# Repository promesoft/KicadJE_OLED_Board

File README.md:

# KicadJE_OLED_Board
uP Boards that uses I2C SSD1306 for OLED Display faceplate

# Purpose
uProcessor board in eurorack units with an SSD1306 OLED display, two rotary dials/pots, two audio inputs, two cv inputs and two outputs. Must match the Faceplate - KicadJE_OLED_Face.
## Board 1 - ATMega32A
Adjustment:  
2 x Encoder  

CV Input:  
2 x ADC AC/DC couple with optional level adj to match 0-5V ADC

Gate or Input Audio:  
2 x ADC AC/DC couple with optional level adj to match 0-5V ADC

Output CV:  
2 x PWM output through 3 pole active LP  
+-10v

Programming Interface:  
ISP  
Serial  

# Status - Initiated
## Initial 
| Stage  | Detail | Status |
| ------------- | ------------- | ------------- |
| create material  | sch | OK
| | pcb | OK
| | gerber | OK
| production |  |  OK
|  | produced  | OK
|  | delivered | OK
## Preliminary validation
| Test  | Detail | Status |
| ------------- | ------------- | ------------- |
| Initial Inspection | | ok |
| Mechanical Inspection | needs longer pins to OLED | ok |
| Initial Technical Test | Board 1 |  |
| Initial Product Test | Board1 |  |

## Secondary validation
| Test  | Detail | Status |
| ------------- | ------------- |------------- |
| Product Test | 1 | |
| Quality | 1 | |
| Long Term Product Test |  |  |
| Power Draw |  | 

## Errata
### Errata - 

## Issues and Notes
### 

# Pictures

# Schematic
## Sch 1

#Software

# Analysis
## Diag 1

## Prototype

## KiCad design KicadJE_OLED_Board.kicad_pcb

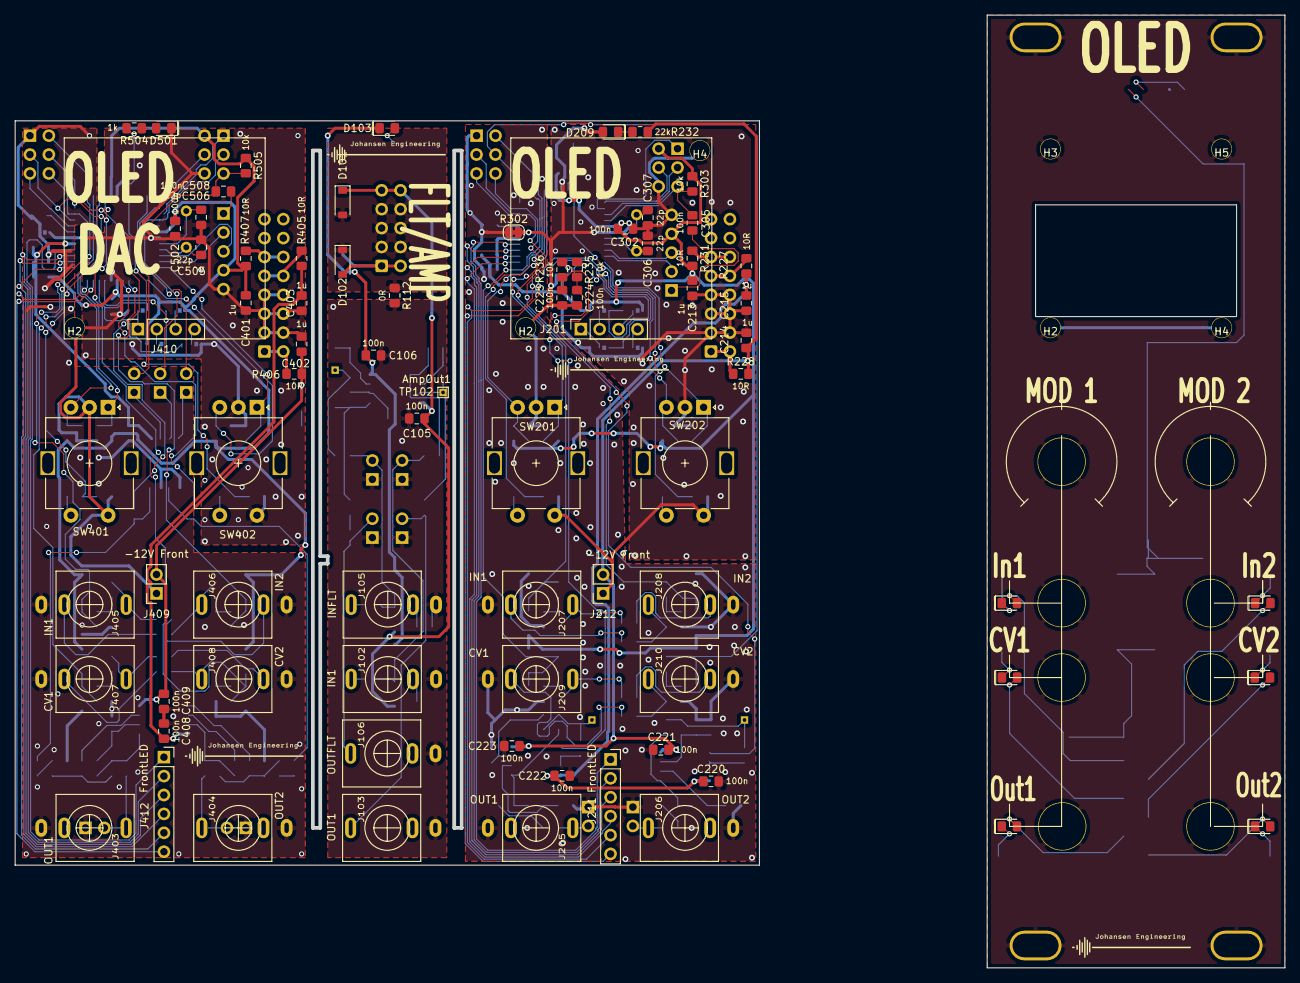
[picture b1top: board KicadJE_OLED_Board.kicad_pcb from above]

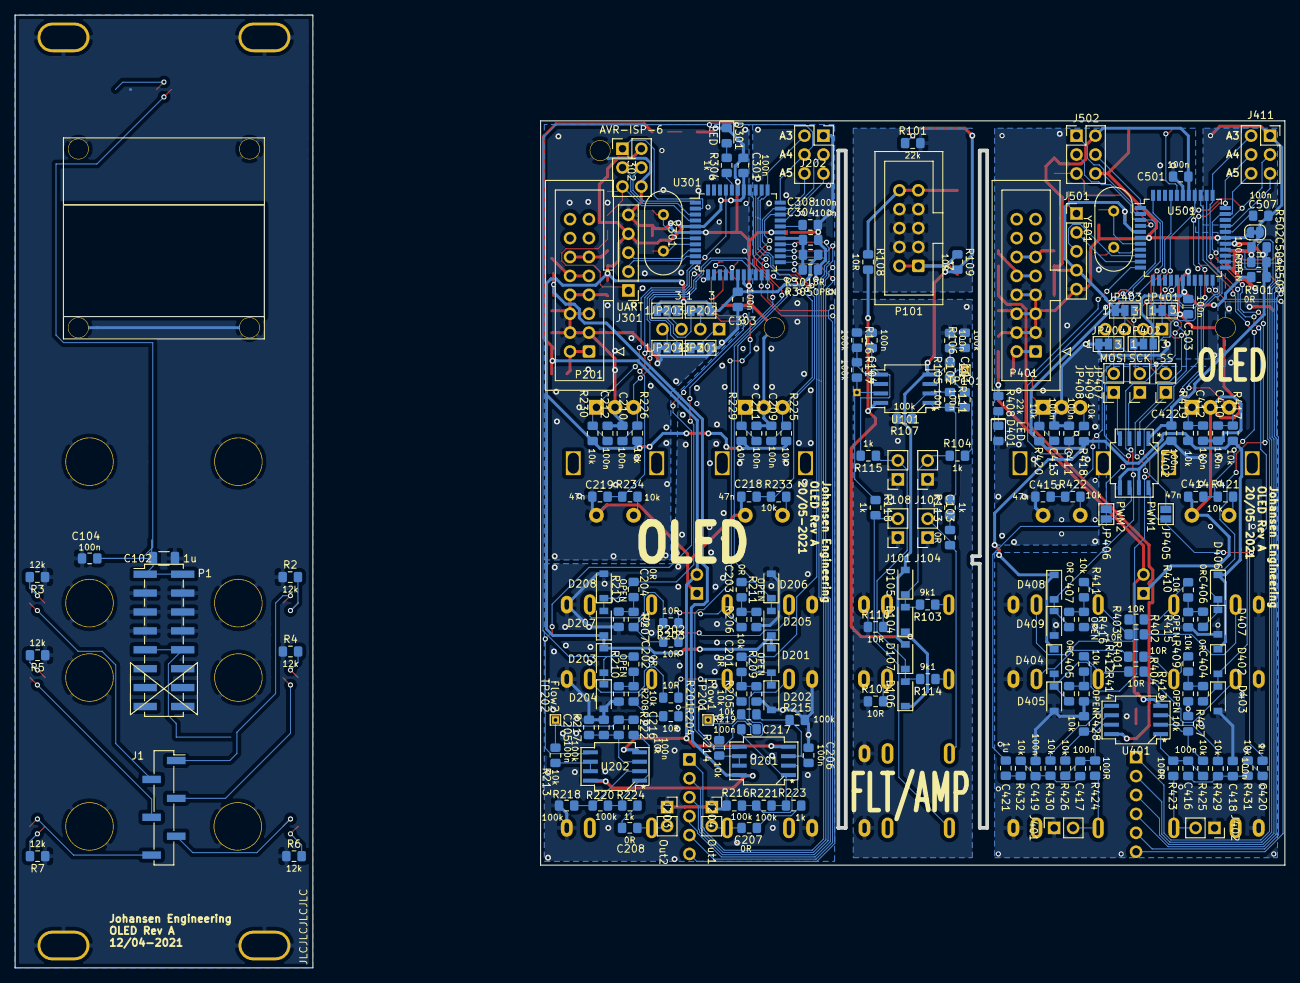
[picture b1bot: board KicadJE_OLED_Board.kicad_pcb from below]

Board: 2 copper layers, 100.0 x 100.0 mm, 296 parts (203 on the bottom side), 184 nets.

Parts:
C101, C102#2, C104, C104#2, C105, C106, C205, C206, C209, C210, C211, C212, C216, C217, C220, C221, C222, C223, C224, C225, C301, C302, C303, C304, C305, C308, C408, C409, C410, C411, C412, C413, C416, C417, C418, C419, C422, C501, C502, C503, C504, C507, C508: 100n; C_0805_AJ
C102: 1u; C_1206_3216Metric
C103, C201, C202, C203, C204, C207, C208, C404, C405, C406, C407: 0R; C_0805_AJ
C213, C214, C215, C401, C402, C403, C420, C421: 1u; C_0805_AJ
C218, C219, C414, C415: 47n; C_0805_AJ
C306, C307, C505, C506: 22p; C_0805_AJ
D4, D5, D6, D7, D8, D9, D103, D209, D301, D401, D501: LED; D_0805_AJ
D101, D102, D104, D105, D106, D107, D201, D202, D203, D204, D205, D206, D207, D208, D402, D403, D404, D405, D406, D407, D408, D409: 1N1007; D_SOD-123
H2, H2#2, H2#3, H3, H4, H4#2, H5: OLED; M2.7_Plated
H102, H103, H104, H105: MountingHole_Pad; MountingHole_Eurorack3
J1: LED 1-6; PinHeader_1x06_P2.54mm_Vertical_SMD_Pin1Right
J101, J204, J402: Out1; PinSocket_1x02_P2.54mm_Vertical
J102, J207, J405: IN1; PJ301SM
J103, J205, J403: OUT1; PJ301SM
J104: OutFlt; PinSocket_1x02_P2.54mm_Vertical
J105: INFLT; PJ301SM
J106: OUTFLT; PJ301SM
J107: In1_Flt; PinSocket_1x02_P2.54mm_Vertical
J108: InAmp; PinSocket_1x02_P2.54mm_Vertical
J201, J410: OLED; PinSocket_1x04_P2.54mm_Vertical
J202, J411: ADC Input; PinSocket_2x03_P2.54mm_Vertical
J203, J401: Out2; PinSocket_1x02_P2.54mm_Vertical
J206, J404: OUT2; PJ301SM
J208, J406: IN2; PJ301SM
J209, J407: CV1; PJ301SM
J210, J408: CV2; PJ301SM
J211, J412: FrontLED; PinSocket_1x06_P2.54mm_Vertical
J212, J409: -12V Front; PinSocket_1x02_P2.54mm_Vertical
J301, J501: UART; PinHeader_1x05_P2.54mm_Vertical
J302, J502: AVR-ISP-6; PinHeader_2x03_P2.54mm_Vertical
JP201, JP401: 1; SolderJumper-3_P1.3mm_Bridged12_Pad1.0x1.5mm_NumberLabels
JP202, JP402: 2; SolderJumper-3_P1.3mm_Bridged12_Pad1.0x1.5mm_NumberLabels
JP203, JP403: 3; SolderJumper-3_P1.3mm_Bridged12_Pad1.0x1.5mm_NumberLabels
JP204, JP404: 4; SolderJumper-3_P1.3mm_Bridged12_Pad1.0x1.5mm_NumberLabels
JP405: PWM1; SolderJumper-2_P1.3mm_Open_Pad1.0x1.5mm
JP406: PWM2; SolderJumper-2_P1.3mm_Open_Pad1.0x1.5mm
JP407: SS; PinSocket_1x02_P2.54mm_Vertical
JP408: MOSI; PinSocket_1x02_P2.54mm_Vertical
JP409: SCK; PinSocket_1x02_P2.54mm_Vertical
P1: Doepfer_Power_16pin; PinHeader_2x08_P2.54mm_Vertical_SMD
P101: Doepfer_Power_10pin; IDC-Header_2x05_P2.54mm_Vertical
P201, P401: Doepfer_Power_16pin; IDC-Header_2x08_P2.54mm_Vertical
R2, R3, R4, R5, R6, R7: 12k; R_0805_AJ
R101, R232, R408: 22k; R_0805_AJ
R102, R108, R109, R110, R201, R202, R203, R204, R227, R228, R231, R401, R402, R403, R404, R405, R406, R407: 10R; R_0805_AJ
R103, R114: 9k1; R_0805_AJ
R104, R113, R115, R118, R223, R224, R304, R504: 1k; R_0805_AJ
R105, R205, R206, R207, R208, R213, R214, R219, R222, R225, R226, R229, R230, R233, R234, R235, R236, R303, R409, R410, R411, R412, R417, R418, R419, R420, R421, R422, R425, R426, R427, R428, R429, R430, R431, R432, R505: 10k; R_0805_AJ
R106, R107, R111, R116, R117, R215, R216, R217, R218, R220, R221: 100k; R_0805_AJ
R112, R301, R501: 0R; R_0805_AJ
R209, R210, R211, R212, R305, R413, R414, R415, R416, R503: OPEN; R_0805_AJ
R302, R502: 0R; SolderJumper-2_P1.3mm_Bridged_RoundedPad1.0x1.5mm
R423, R424: 100R; R_0805_AJ
SW201, SW202, SW401, SW402: Rotary_Encoder_Switch; RotaryEncoder_Alps_EC11E-Switch_Vertical_H20mm
TP101, TP201: Flow1; TestPoint_THTPad_1.0x1.0mm_Drill0.5mm
TP102: SQ; Jack_6m3
TP102#2: AmpOut1; TestPoint_THTPad_1.0x1.0mm_Drill0.5mm
TP103: In1; Jack_6m3
TP105: In3; Jack_6m3
TP106: HS; Jack_6m3
TP107: OFF1; Pot_6m3_scale1
TP107#2: FM; Jack_6m3
TP108: PWM; Jack_6m3
TP112: Fine; Pot_6m3_scale1
TP202: Flow2; TestPoint_THTPad_1.0x1.0mm_Drill0.5mm
U101, U201, U202, U401: TL072; AJ_SO-8_5.3x6.2mm_P1.27mm
U301, U501: ATmega32A-AU; TQFP-44_10x10mm_P0.8mm
U402: MCP4822; AJ_SO-8_5.3x6.2mm_P1.27mm
Y301, Y501: 16MHz; Crystal_HC49-U_Vertical

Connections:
10_INT0: C212.1, R230.2, SW202.A, U301.11
10_INT0_DAC: C413.1, R420.2, SW402.A, U501.11
11_INT1: C210.1, R226.1, SW202.B, U301.12
11_INT1_DAC: C411.1, R418.1, SW402.B, U501.12
24_A0: C218.1, R233.1, U301.37
24_A0_DAC: C414.1, R421.1, U501.37
25_A1: C211.1, R229.2, SW201.A, U301.36
25_A1_DAC: C412.1, R419.2, SW401.A, U501.36
26_A2: C209.1, R225.1, SW201.B, U301.35
26_A2_DAC: C410.1, R417.1, SW401.B, U501.35
27_A3: C201.2, D201.2, D202.1, J202.2, U301.34
27_A3_DAC: C404.2, D402.2, D403.1, J411.2, U501.34
28_A4: C202.2, D203.2, D204.1, J202.4, U301.33
28_A4_DAC: C405.2, D404.2, D405.1, J411.4, U501.33
29_A5: C203.2, D205.2, D206.1, J202.6, U301.32
29_A5_DAC: C406.2, D406.2, D407.1, J411.6, U501.32
30_A6: C204.2, D207.2, D208.1, J202.3, U301.31
30_A6_DAC: C407.2, D408.2, D409.1, J411.3, U501.31
31_A7: J202.5, U301.30
31_A7_DAC: J411.5, U501.30
+5V: C213.2, C301.2, C302.2, C303.2, C401.2, C501.2, C502.2, C503.2, D201.1, D203.1, D205.1, D207.1, D402.1, D404.1, D406.1, D408.1, J301.4, J302.2, J501.4, J502.2, JP202.3, JP203.1, JP402.3, JP403.1, P1.11, P1.12, R225.2, R226.2, R229.1, R230.1, R231.2, R301.2, R303.1, R407.2, R417.2, R418.2, R419.1, R420.1, R501.2, R505.1, U301.5, U301.17, U301.38, U501.5, U501.17, U501.38
+5VA: C304.2, C422.1, C504.2, R301.1, R305.1, R501.1, R503.1, U301.27, U402.1, U501.27
+12V: C215.2, C220.1, C222.1, C403.2, C408.1, R227.2, R405.2, U201.8, U202.8, U401.8
+12VA: C105.1, D104.1, D106.1, P1.9, P1.10, R108.2, U101.8
-12V: C214.2, C221.2, C223.2, C402.2, C409.2, J212.2, J409.2, R228.2, R232.2, R406.2, R408.2, U201.4, U202.4, U401.4
-12VA: C102.2, C104.2, C106.2, D103.1, D105.2, D107.2, P1.1, P1.2, R109.2, U101.4
/InNeg: D102.2, P101.1, P101.2, R109.1
/InPos: D101.1, P101.9, P101.10, R108.1
/KicadJE_ATMega32A_DAC/1_inv: R425.1, R427.2, U401.2
/KicadJE_ATMega32A_DAC/1_noninv: R429.2, U401.3
/KicadJE_ATMega32A_DAC/1_out: C416.1, R423.1, R425.2, U401.1
/KicadJE_ATMega32A_DAC/2_inv: R426.1, R428.2, U401.6
/KicadJE_ATMega32A_DAC/2_noninv: R430.2, U401.5
/KicadJE_ATMega32A_DAC/2_out: C417.1, R424.1, R426.2, U401.7
/KicadJE_ATMega32A_DAC/In5V: P401.11, P401.12, R407.1
/KicadJE_ATMega32A_DAC/InNeg: P401.1, P401.2, R406.1
/KicadJE_ATMega32A_DAC/InPos: P401.9, P401.10, R405.1
/KicadJE_ATMega32A_DAC/SCK: JP409.1, U402.3
/KicadJE_ATMega32A_DAC/SDI: JP408.1, U402.4
/KicadJE_ATMega32A_DAC/SS: JP407.1, U402.2
/KicadJE_ATMega32A_DAC/sheet6241082B/0_LED: R504.2, U501.40
/KicadJE_ATMega32A_DAC/sheet6241082B/D6_MISO: J502.1, U501.2
/KicadJE_ATMega32A_DAC/sheet6241082B/D8_Rx: J501.3, U501.9
/KicadJE_ATMega32A_DAC/sheet6241082B/D9_Tx: J501.2, U501.10
/KicadJE_ATMega32A_DAC/sheet6241082B/D16_SCL: JP402.1, JP403.3, U501.19
/KicadJE_ATMega32A_DAC/sheet6241082B/D17_SDA: JP401.1, JP404.3, U501.20
/KicadJE_ATMega32A_DAC/sheet6241082B/D18: J412.6, U501.21
/KicadJE_ATMega32A_DAC/sheet6241082B/D19: J412.5, U501.22
/KicadJE_ATMega32A_DAC/sheet6241082B/D20: J412.4, U501.23
/KicadJE_ATMega32A_DAC/sheet6241082B/D21: J412.3, U501.24
/KicadJE_ATMega32A_DAC/sheet6241082B/D22: J412.2, U501.25
/KicadJE_ATMega32A_DAC/sheet6241082B/D23: J412.1, U501.26
/KicadJE_OLED_Mega32/ATMega32A.sch/0_LED: R304.2, U301.40
/KicadJE_OLED_Mega32/ATMega32A.sch/D5_MOSI: J302.4, U301.1
/KicadJE_OLED_Mega32/ATMega32A.sch/D6_MISO: J302.1, U301.2
/KicadJE_OLED_Mega32/ATMega32A.sch/D7_SCK: J302.3, U301.3
/KicadJE_OLED_Mega32/ATMega32A.sch/D8_Rx: J301.3, U301.9
/KicadJE_OLED_Mega32/ATMega32A.sch/D9_Tx: J301.2, U301.10
/KicadJE_OLED_Mega32/ATMega32A.sch/D16_SCL: JP202.1, JP203.3, U301.19
/KicadJE_OLED_Mega32/ATMega32A.sch/D17_SDA: JP201.1, JP204.3, U301.20
/KicadJE_OLED_Mega32/ATMega32A.sch/D18: J211.6, U301.21
/KicadJE_OLED_Mega32/ATMega32A.sch/D19: J211.5, U301.22
/KicadJE_OLED_Mega32/ATMega32A.sch/D20: J211.4, U301.23
/KicadJE_OLED_Mega32/ATMega32A.sch/D21: J211.3, U301.24
/KicadJE_OLED_Mega32/ATMega32A.sch/D22: J211.2, U301.25
/KicadJE_OLED_Mega32/ATMega32A.sch/D23: J211.1, U301.26
/KicadJE_OLED_Mega32/In5V: P201.11, P201.12, R231.1
/KicadJE_OLED_Mega32/InNeg: P201.1, P201.2, R228.1
/KicadJE_OLED_Mega32/InPos: P201.9, P201.10, R227.1
CS_DAC: JP407.2, U501.44
CV1_32: J209.T, R201.1, R205.1
CV1_32_DAC: J407.T, R401.1, R409.1
CV2_32: J210.T, R204.1, R208.1
CV2_32_DAC: J408.T, R404.1, R412.1
D1: C219.1, R234.1, U301.41
D1_DAC: C415.1, R422.1, U501.41
DACA: C420.2, JP405.2, U402.8
DACB: C421.2, JP406.2, U402.6
Flow1_32: R235.1, U301.15
Flow1_32_DAC: JP405.1, U501.15
Flow2_32: R236.1, U301.16
Flow2_32_DAC: JP406.1, U501.16
GND: C102.1, C104.1, C209.2, C210.2, C211.2, C212.2, C213.1, C214.1, C215.1, C218.2, C219.2, C224.2, C225.2, C301.1, C302.1, C303.1, C306.2, C307.2, C401.1, C402.1, C403.1, C410.2, C411.2, C412.2, C413.2, C414.2, C415.2, C501.1, C502.1, C503.1, C505.2, C506.2, D101.2, D102.1, D209.2, D301.1, D401.2, D501.1, H2.1, H2#2.1, H2#3.1, H3.1, H4.1, H4#2.1, H5.1, H102.1, H103.1, H104.1, H105.1, J212.1, J301.5, J302.6, J409.1, J501.5, J502.6, JP201.3, JP204.1, JP401.3, JP404.1, P1.3, P1.4, P1.5, P1.6, P1.7, P1.8, P101.3, P101.4, P101.5, P101.6, P101.7, P101.8, P201.3, P201.4, P201.5, P201.6, P201.7, P201.8, P401.3, P401.4, P401.5, P401.6, P401.7, P401.8, R2.1, R3.1, R4.1, R5.1, R6.1, R7.1, R101.2, R112.1, R302.2, R502.2, SW201.C, SW201.S2, SW202.C, SW202.S2, SW401.C, SW401.S2, SW402.C, SW402.S2, TP102.1, TP103.1, TP105.1, TP106.1, TP107.1, TP107#2.1, TP108.1, TP112.1, U301.6, U301.18, U301.28, U301.39, U501.6, U501.18, U501.28, U501.39
GNDA: C102#2.2, C104#2.2, C105.2, C106.1, C205.2, C206.2, C220.2, C221.1, C222.2, C223.1, C304.1, C308.2, C408.2, C409.1, C418.2, C419.2, C422.2, C504.1, C507.2, D202.2, D204.2, D206.2, D208.2, D403.2, D405.2, D407.2, D409.2, J101.1, J102.S, J103.S, J104.1, J105.S, J106.S, J107.1, J108.1, J202.1, J203.1, J204.1, J205.S, J206.S, J207.S, J208.S, J209.S, J210.S, J401.1, J402.1, J403.S, J404.S, J405.S, J406.S, J407.S, J408.S, J411.1, R102.1, R106.2, R107.2, R110.1, R112.2, R116.1, R209.2, R210.2, R211.2, R212.2, R215.2, R216.2, R217.2, R218.2, R302.1, R305.2, R413.2, R414.2, R415.2, R416.2, R427.1, R428.1, R502.1, R503.2, U402.5, U402.7
In1_32: J207.T, R203.1, R206.1
In1_32_DAC: J405.T, R403.1, R410.1
In1_Amp: J102.T, R114.1
In1_Filt: J105.T, R103.1
In2_32: J208.T, R202.1, R207.1
In2_32_DAC: J406.T, R402.1, R411.1
MOSI_DAC: J502.4, JP408.2, U501.1
unnamed: C101.1, R104.2, R105.1, TP101.1
unnamed: C101.2, R111.2, R113.2, U101.1
unnamed: C102#2.1, R105.2, R106.1, U101.3
unnamed: C103.1, R113.1
unnamed: C104#2.1, R115.2, U101.5
unnamed: C201.1, R205.2, R209.1
unnamed: C202.1, R208.2, R210.1
unnamed: C203.1, R206.2, R211.1
unnamed: C204.1, R207.2, R212.1
unnamed: C205.1, R217.1, R222.2, U202.3
unnamed: C206.1, R215.1, R219.2, U201.3
unnamed: C207.1, R223.1
unnamed: C208.1, R224.1
unnamed: C216.1, R213.2, R222.1, TP202.1
unnamed: C216.2, R220.1, R224.2, U202.1
unnamed: C217.1, R214.2, R219.1, TP201.1
unnamed: C217.2, R221.2, R223.2, U201.1
unnamed: C224.1, R235.2, U201.5
unnamed: C225.1, R236.2, U202.5
unnamed: C305.2, J301.1
unnamed: C306.1, U301.8, Y301.1
unnamed: C307.1, U301.7, Y301.2
unnamed: C308.1, U301.29
unnamed: C404.1, R409.2, R413.1
unnamed: C405.1, R412.2, R414.1
unnamed: C406.1, R410.2, R415.1
unnamed: C407.1, R411.2, R416.1
unnamed: C416.2, C418.1, R429.1, R431.2
unnamed: C417.2, C419.1, R430.1, R432.2
unnamed: C420.1, R431.1
unnamed: C421.1, R432.1
unnamed: C505.1, U501.8, Y501.1
unnamed: C506.1, U501.7, Y501.2
unnamed: C507.1, U501.29
unnamed: C508.2, J501.1
unnamed: D4.1, R2.2
unnamed: D4.2, J1.1
unnamed: D5.1, R3.2
unnamed: D5.2, J1.2
unnamed: D6.1, R4.2
unnamed: D6.2, J1.3
unnamed: D7.1, R5.2
unnamed: D7.2, J1.4
unnamed: D8.1, R6.2
unnamed: D8.2, J1.5
unnamed: D9.1, R7.2
unnamed: D9.2, J1.6
unnamed: D103.2, R101.1
unnamed: D104.2, D105.1, J107.2, R103.2, R104.1
unnamed: D106.2, D107.1, J108.2, R114.2, R115.1
unnamed: D209.1, R232.1
unnamed: D301.2, R304.1
unnamed: D401.1, R408.1
unnamed: D501.2, R504.1
unnamed: J102.TN, R102.2
unnamed: J105.TN, R110.2
unnamed: J201.1, JP201.2
unnamed: J201.2, JP202.2
unnamed: J201.3, JP203.2
unnamed: J201.4, JP204.2
unnamed: J207.TN, R202.2
unnamed: J208.TN, R203.2
unnamed: J209.TN, R204.2
unnamed: J210.TN, R201.2
unnamed: J405.TN, R402.2
unnamed: J406.TN, R403.2
unnamed: J407.TN, R404.2
unnamed: J408.TN, R401.2
unnamed: J410.1, JP401.2
unnamed: J410.2, JP402.2
unnamed: J410.3, JP403.2
unnamed: J410.4, JP404.2
unnamed: P1.13, P1.14
unnamed: P1.15, P1.16
unnamed: R107.1, R111.1, U101.2
unnamed: R116.2, R117.1, U101.6
unnamed: R117.2, R118.1, TP102#2.1, U101.7
unnamed: R213.1, U202.6, U202.7
unnamed: R214.1, U201.6, U201.7
unnamed: R216.1, R221.1, U201.2
unnamed: R218.1, R220.2, U202.2
unnamed: R233.2, SW201.S1
unnamed: R234.2, SW202.S1
unnamed: R421.2, SW401.S1
unnamed: R422.2, SW402.S1
OUT1_DAC: J402.2, J403.T, R423.2
OUT2_DAC: J401.2, J404.T, R424.2
Out1_32: C207.2, J204.2, J205.T
Out1_Amp: J101.2, J103.T, R118.2
Out1_Filt: C103.2, J104.2, J106.T
Out2_32: C208.2, J203.2, J206.T
SCK_DAC: J502.3, JP409.2, U501.3
reset: C305.1, C508.1, J302.5, J502.5, R303.2, R505.2, U301.4, U501.4

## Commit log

2021-04-29 initiation
2021-04-30 Changing source of PCB template
2021-04-30 Updating Atmega32A subboard
2021-04-30 Placing hierarchical labels on ATMega32A
2021-04-30 Subboard done
2021-04-30 Aref resolved - OLED in sch
2021-04-30 Front LED
2021-04-30 Cleanup MasterSCH
2021-04-30 Importing Encoder from Midi2CV
2021-05-01 In/CV+Encoder matched to analog input
2021-05-04 5VA on Atmega32A
2021-05-04 Initial footprints and netlist
2021-05-04 PCB outline
2021-05-04 Footprint upd
2021-05-04 Encoder 2
2021-05-04 Component place
2021-05-04 cleanup and rename sch subs
2021-05-04 Most components placed
2021-05-04 Sallen Key LP filter added to output
2021-05-04 6pin input hdr
2021-05-04 Added buffer for output
2021-05-04 Components placed for KicadJE_OLED_Mega32
2021-05-06 Small Amp/Filter circuit
2021-05-07 Filt/Amp Netlist
2021-05-07 Edgecuts
2021-05-09 Amp/Filt
2021-05-09 move pinhdr from in jacks to input circuit
    after protection resistor - so pcb may be cut above the connectors in case this is needed
2021-05-09 placed amp/filt
2021-05-10 Sheet 2 - ATMega32A DAC
2021-05-10 annotate dac
2021-05-10 footprints dac
2021-05-10 Placing DAC
2021-05-11 Components placed
2021-05-14 Netclases
2021-05-14 Power Amp/FLT
2021-05-16 Board
2021-05-16 Wiring DAC board - initiated
2021-05-16 Initial DAC layout
2021-05-18 Update KicadJE_OLED_Board.kicad_pcb
    All boards routed initially
2021-05-18 DRC
    DRC
2021-05-18 D1 -> D1_DAC
2021-05-18 Update KicadJE_OLED_Board.kicad_pcb
    D1__Dac on PCB
2021-05-18 Pictures of the board before label adj
2021-05-19 Front Labels
2021-05-19 3D Amp
2021-05-20 Update KicadJE_OLED_Board.kicad_pcb
    Starting to label back
2021-05-20 Update KicadJE_OLED_Board.kicad_pcb
    DAC Labeled bottom
2021-05-20 Update KicadJE_OLED_Board.kicad_pcb
    Logo
2021-05-20 Update KicadJE_OLED_Board.kicad_pcb
    Labels
2021-05-20 Update KicadJE_OLED_Board.kicad_pcb
    Labels done
2021-05-20 DRC done
2021-05-20 Pict
2021-05-20 Gerber
2021-05-20 BoardOnlyPCB+Gerber
